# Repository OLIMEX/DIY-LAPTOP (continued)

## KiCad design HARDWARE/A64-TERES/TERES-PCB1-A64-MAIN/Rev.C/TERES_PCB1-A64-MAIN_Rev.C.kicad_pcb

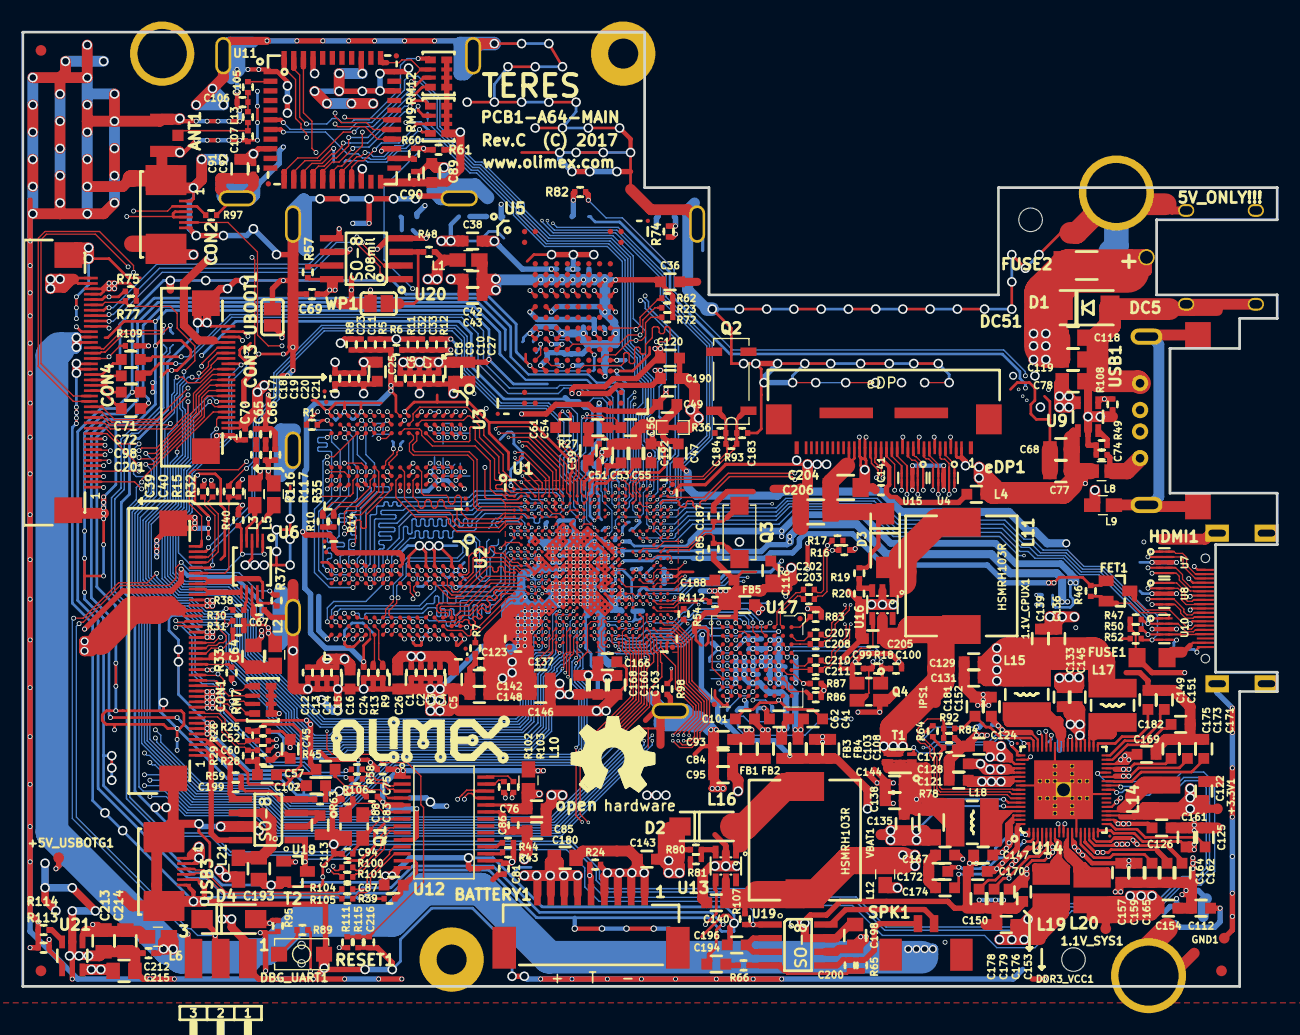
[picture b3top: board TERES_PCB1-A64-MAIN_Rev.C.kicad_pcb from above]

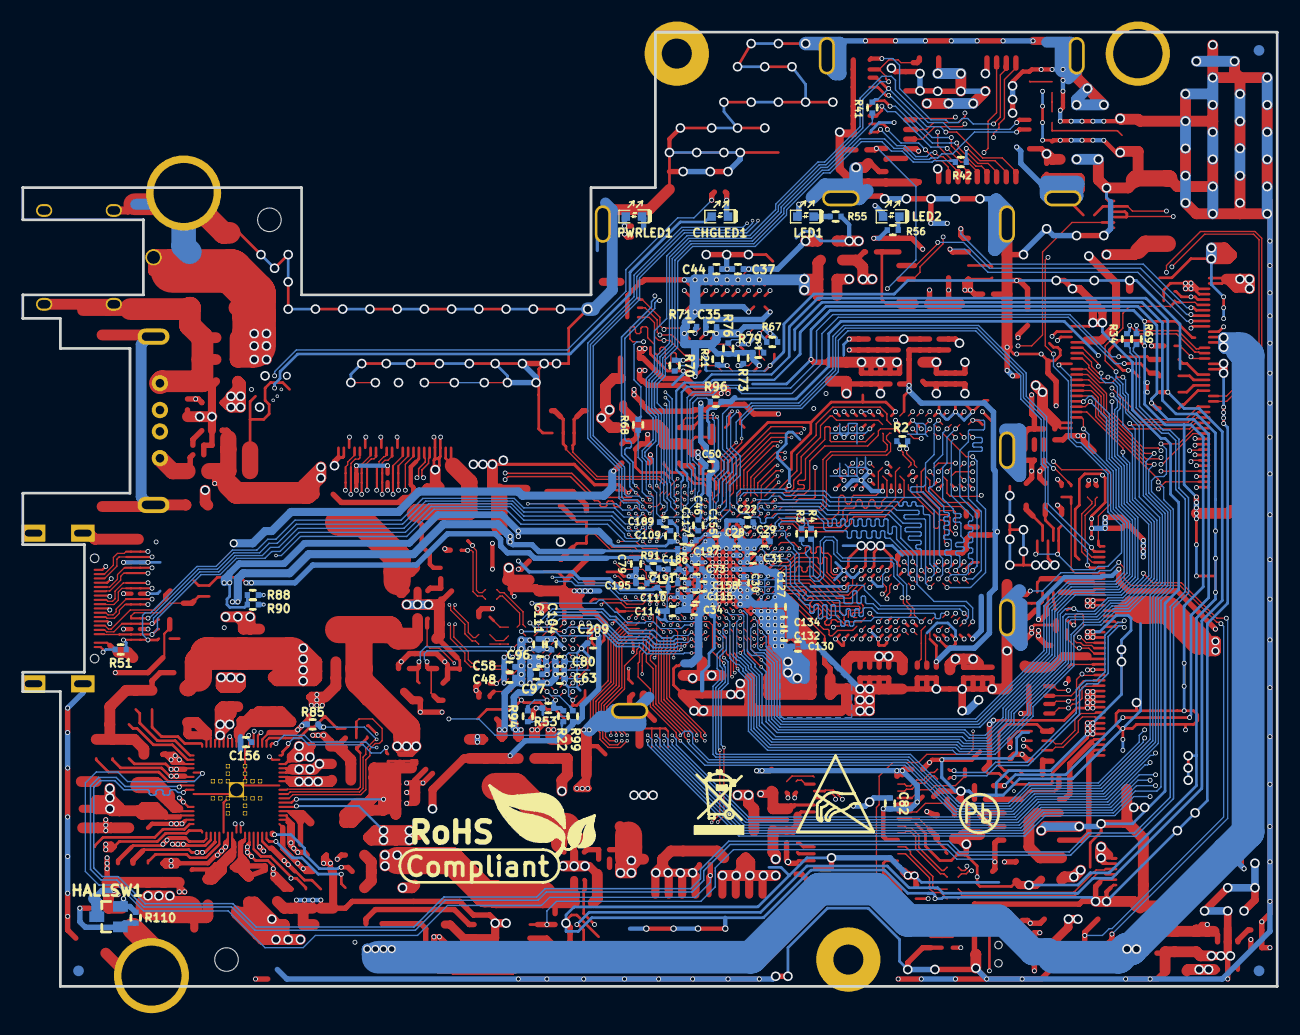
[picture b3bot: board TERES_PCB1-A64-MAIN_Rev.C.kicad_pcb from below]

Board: 6 copper layers, 117.0 x 89.0 mm, 443 parts (75 on the bottom side), 414 nets.

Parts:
1.1V_CPUX1, 1.1V_SYS1: TESTPAD; TESTPAD_40-ROUND
+3.3V1: TESTPAD; TESTPAD_40-ROUND
+5V_USBOTG1: +5V_USBOTG; TESTPAD_40-ROUND
ANT1: PCB_WIFI_ANT; U.FL-R-SMT-1
BATTERY1: BATTCON; BATCONN-TERES
C1, C2, C3, C4, C6, C7, C8, C9, C11, C12, C13, C14, C15, C17, C18, C19, C20, C22, C23, C24, C25, C28, C29, C30, C31, C32, C33, C34, C35, C37, C39, C40, C44, C46, C50, C51, C52, C60, C65, C66, C67, C69, C70, C73, C74, C75, C79, C81, C82, C83, C86, C90, C92, C109, C110, C114, C115, C117, C123, C127, C130, C132, C134, C141, C155, C156, C158, C177, C186, C189, C191, C195, C197, C202, C203, C207, C208, C209, C210, C211, C212, C216: 100nF; C_0402_5MIL_DWS
C5, C10, C16, C21, C26, C42, C47, C49, C53, C54, C57, C59, C89, C91, C116, C121, C122, C124, C125, C126, C128, C129, C131, C133, C136, C138, C139, C140, C143, C144, C145, C146, C147, C148, C149, C150, C151, C152, C153, C154, C157, C159, C161, C162, C164, C165, C166, C167, C168, C169, C170, C171, C172, C173, C175, C176, C178, C179, C188, C192: 10uF/6.3V/0603; C_0603_5MIL_DWS
C27, C36, C38, C43, C45, C55, C71, C72, C98, C102, C112, C113, C120, C135, C137, C142, C160, C163, C181, C182, C190, C194, C196, C201: 1uF/6.3V/0603; C_0603_5MIL_DWS
C41, C62, C93, C101: 4.7uF/6.3V; C_0603_5MIL_DWS
C48, C63, C96, C104: 100nF/6.3V; C_0402_5MIL_DWS
C56, C61: 2.2uF/6.3V/0603; C_0603_5MIL_DWS
C58, C80, C97, C111: 10nF/6.3V; C_0402_5MIL_DWS
C64, C68, C77, C78, C118, C119, C180, C213, C214, C215: 47uF/6.3V/0805; C_0805_5MIL_DWS
C76: 10uF; C_0603_5MIL_DWS
C84, C95, C103, C108, C205: 22uF/6.3V; C_0603_5MIL_DWS
C85: 10uF; R_0603_5MIL_DWS
C87: 1uF; C_0603_5MIL_DWS
C88, C94, C185, C187: 33pF; C_0402_5MIL_DWS
C99, C100: 22pF; C_0402_5MIL_DWS
C105, C183, C184: 10pF; C_0402_5MIL_DWS
C106: 0.8pF; C_0402_5MIL_DWS
C107: 1.5pF; C_0402_5MIL_DWS
C174: NA(10uF/6.3V/0603); C_0603_5MIL_DWS
C193, C198: 47uF; C_0805_5MIL_DWS
C199, C200: 100pF; C_0402_5MIL_DWS
C204, C206: 22uF/25V; C_1206_5MIL_DWS
CHGLED1: LED/RED/0603; LED_0603_KA
CON1, CON4: CONN_01X40; FPV-WZA21-40-LF
CON2: CONN_01X06; FLEXCON-0.5-6
CON3: CONN_01X20; FPV-WZA21-20-LF
D1: SMBJ6.0A; DO214AA
D2, D3, D4: 1N5822/SS34/SMA; SMA-KA
DBG_UART1: NA(HN1x3); HN1x3(SMD)
DC5: PWR-JACK-THERES; DC-055-TERES
DC51: TESTPAD; TESTPAD_40-ROUND
DDR3_VCC1: TESTPAD; TESTPAD_40-ROUND
FB1, FB2, FB3, FB4, FB5: FB0603/600R/200mA; L_0603_5MIL_DWS
FET1: BSS138(SOT23-3); SOT23
FUSE1: FSMD035; FUSE-1206
FUSE2: NA(5025); FUSE-5025
GND1: TESTPAD; TESTPAD_40-ROUND
HALLSW1: TCS40DPR; SOT23
HDMI1: HDMI-SWM-19; HDMI-MINI-TERES
HOLE1, HOLE2, HOLE3, HOLE4, HOLE5, HOLE6, HOLE7, HOLE8, HOLE9: TESTPAD; Oval_Drill
IPS1: TESTPAD; TESTPAD_40-ROUND
L1, L2, L3, L5, L6, L8, L9, L10, L12, L21: FB0805/600R/2A; L_0805_5MIL_DWS
L4: FB0603/600R/200mA; L_0603_5MIL_DWS
L11: HSMRH103R-220M; HSMRH103R
L13: 3.3nH; R_0402_5MIL_DWS
L14, L19, L20: SWPA3015S1R5NT(1.5uH/2.30A/DCR<0.1R/CD32); CD32
L15, L17, L18: SWPA4018S1R5NT(1.5uH/3.35A/DCR<0.1R/CD43); CD42(43)
L16: HSMRH103R-2R5M; HSMRH103R
LED1, LED2: GREEN; LED_0603_KA
MountingHole: Mounting_hole_3.3mm; Mounting_hole_5.6mm_TERES
MountingHole#2: Mounting_hole_3.3mm; Mounting_hole_5.6mm_TERES
MountingHole#3: Mounting_hole_3.3mm
MountingHole#4: Mounting_hole_3.3mm; Mounting_hole_2.8mm
MountingHole#5: Mounting_hole_3.3mm; Mounting_hole_TERES_4.6mm
MountingHole#6, MountingHole#7: Mounting_hole_3.3mm; NPTH_2.2mm
PWRLED1: LED/Green/0603; LED_0603_KA
Q1: 12MHz-20pf; TSX-3.2x2.5mm_GND(3)
Q2: MC-306_32.768KHZ/SMD_8038/6pF; MC306-HS
Q3: 4SB24.000F20E15/5x3.2mm/20ppm/20pF; Q5x3.25
Q4: 27.000MHz/20ppm; TSX-3.2x2.5mm_GND(3)
R1, R5, R8, R11, R12, R74: 2k/1%; R_0402_5MIL_DWS
R2: 100R/1%; R_0402_5MIL_DWS
R3, R4, R33, R34, R41, R42, R54, R58, R68, R69, R100, R101, R102, R103, R104, R105, R106, R116, R117: 22R; R_0402_5MIL_DWS
R6, R62, R70, R71, R72, R73, R76, R79, R96, R97, R98: NA; R_0402_5MIL_DWS
R7, R9, R10: 240R/1%; R_0402_5MIL_DWS
R13, R14: NA(243R/1%); R_0402_5MIL_DWS
R15: 47K; R_0402_5MIL_DWS
R16, R17: (na)100K; R_0402_5MIL_DWS
R18, R32: 1M; R_0402_5MIL_DWS
R19: 22.1K /1%; R_0402_5MIL_DWS
R20: 1.1K/1%; R_0402_5MIL_DWS
R21, R23, R31, R39, R40, R43, R48, R52, R57, R85, R95, R108, R109, R110, R113, R115: 10k; R_0402_5MIL_DWS
R22, R25, R28, R64, R86, R89, R92: 1k; R_0402_5MIL_DWS
R24: NA(10K); R_0402_5MIL_DWS
R26, R29, R55, R56: 1.5k; R_0402_5MIL_DWS
R27: 200k/1%; R_0402_5MIL_DWS
R30, R35, R53: 100k; R_0402_5MIL_DWS
R36: 0R(Board_Mounted); 0R_0603
R37, R38: 220R; R_0402_5MIL_DWS
R44, R46, R67: 47k; R_0402_5MIL_DWS
R45: 680R/1%; R_0603_5MIL_DWS
R47, R50, R82, R87, R88, R90, R94, R99, R112: 2.2k; R_0402_5MIL_DWS
R49: 10k/1%; R_0402_5MIL_DWS
R51, R75, R77, R111: 4.7k; R_0402_5MIL_DWS
R59, R65: 22.1K/1%; R_0402_5MIL_DWS
R60, R91: NA(0R); R_0402_5MIL_DWS
R61: NA(10k); R_0402_5MIL_DWS
R63, R66: 12k/1%; R_0402_5MIL_DWS
R78: 0.01R/1%/1206; R_1206_5MIL_DWS
R80: 8.25k/1%; R_0402_5MIL_DWS
R81: 1.1k/1%; R_0402_5MIL_DWS
R83: 12K_1%; R_0402_5MIL_DWS
R84: na(1k); R_0402_5MIL_DWS
R93: 10M; R_0402_5MIL_DWS
R107: 150K; R_0402_5MIL_DWS
R114: 13k/1%; R_0402_5MIL_DWS
RESET1: IT1185AU2; uTACTIL
RM7, RM9, RM12: RA1206_(4x0603)_4B8_100k; R_MATRIX_4
Ref**: Val**; LOGO_ANTISTATIC_1
Ref**#2: Val**; LOGO_ROHS_1
SPK1: SPK1; CON-SPK-TERES
T1: WPM1481(DFN2X2-6L); DFN2x2-6L
T2: DTC114YKA(SOT-23); SOT23
U1: AllWinner-A64(FBGA396); FBGA396
U2, U3: K4B4G1646Q-HYK0(FBGA-96_256Mx16_DDR3-1600_11-11-1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; FBGA96(HYNIX_SAMSUNG_512MX16_DDR3)
U4, U7, U8, U10, U15: RCLAMP0524P(SLP2510P8); SLP2510P8
U5: MTFC4GACAANA-4M_IT(TBGA100); TBGA100
U6: TS5A23159; VSSOP-10
U9, U21: SY6280AAC(SOT23-5); SOT-23-5
U11: RTL8723BS(ComboModule); RL-SM02BD(RTL8723BS)
U12: GL850G-SO28; SSOP28
U13, U16: MT3608(SOT23-6); SOT23-6
U14: AXP803(QFN68_8x8mm); QFN68
U17: ANX6345; BGA_8x8mm_81p_0.8
U18, U19: TS4871; SO-8
U20: W25Q128FVSSIG; SO-8_208mil
UBOOT1: Open; SJ
USB1: USB_A_THERES; USB-A-TERES
USB3: USB3; FLEXCON-0.5-6
VBAT1: TESTPAD; TESTPAD_40-ROUND
WP1: Open; SJ
eDP1: LCD_CONN; eDP-TERES

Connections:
1.1V_CPUS: C117.2, C120.2, C179.2, U1.H15, U14.5
1.1V_CPUX: 1.1V_CPUX1.1, C123.2, C127.2, C129.2, C130.2, C131.2, C132.2, C134.2, C136.2, C137.2, C139.2, C142.2, C146.2, C148.2, L15.2, L17.2, U1.AA1, U1.AA3, U1.AB2, U1.AC1, U1.AC2, U1.U6, U1.V2, U1.V3, U1.V4, U1.V5, U1.V6, U1.W1, U1.W3, U1.W4, U1.W5, U1.Y2, U1.Y3, U1.Y4
1.1V_SYS: 1.1V_SYS1.1, C154.2, C155.2, C158.2, C160.2, C163.2, C166.2, C168.2, L20.2, U1.J12, U1.J13, U1.K14, U1.L13, U1.L14, U1.M13, U1.M14, U1.N14, U1.P14, U1.R13, U1.R14, U1.T15, U14.9
1.2V_HSIC: C178.2, C197.1, CON3.17, U1.K16, U14.3
3.0V_RTC: C152.1, C189.2, C190.2, R85.2, U1.H16, U14.49
#DEBUGSELECT: R40.2, U1.D20, U6.1, U6.5
+1.5V: C1.1, C2.1, C3.1, C4.1, C5.1, C6.1, C7.1, C8.1, C9.1, C10.1, C11.1, C12.1, C13.1, C14.1, C15.1, C16.1, C17.1, C18.1, C19.1, C20.1, C21.1, C26.1, C27.1, C28.1, C29.1, C30.1, C31.1, C32.2, C150.2, DDR3_VCC1.1, L19.2, R1.2, R5.2, R11.2, U1.G7, U1.G8, U1.G9, U1.J8, U1.K6, U1.K7, U1.L6, U1.L7, U1.L8, U1.N7, U1.N8, U2.A1, U2.A8, U2.B2, U2.C1, U2.C9, U2.D2, U2.D9, U2.E9, U2.F1, U2.G7, U2.H2, U2.H9, U2.K2, U2.K8, U2.N1, U2.N9, U2.R1, U2.R9, U3.A1, U3.A8, U3.B2, U3.C1, U3.C9, U3.D2, U3.D9, U3.E9, U3.F1, U3.G7, U3.H2, U3.H9, U3.K2, U3.K8, U3.N1, U3.N9, U3.R1, U3.R9, U14.8
+1V8: C47.2, C50.2, C170.2, U1.E13, U14.68
+3.0VA: C46.1, C49.1, C175.1, C191.2, R32.2, U1.G14, U1.N16, U14.31
+3.3VD: C79.2, C161.2, FET1.1, R46.1, U1.M16, U14.17
+3V3: +3.3V1.1, C34.2, C69.2, C70.2, C73.2, C91.2, C92.2, C112.2, C114.2, C115.2, C116.2, C122.2, C195.2, CON3.1, CON3.2, CON4.37, CON4.38, HALLSW1.1, L1.1, L2.1, L14.2, R16.1, R30.2, R31.2, R48.2, R57.2, R74.1, R75.1, R77.1, R91.1, R95.2, R109.2, R110.2, RM7.1.1, RM7.2.1, RM7.3.1, RM7.4.1, U1.L16, U1.N19, U1.R16, U1.T14, U1.U15, U1.U18, U11.9, U13.4, U14.20, U20.8, eDP1.1, eDP1.2
+5V: C78.1, C143.2, C215.1, D2.1, R80.1, U9.5, U21.5
/NAND Flash , eMMC, T-Card and Audio/FC_MIC_N: C60.1, CON1.8, R29.1
/NAND Flash , eMMC, T-Card and Audio/FC_MIC_P: C52.1, CON1.9, R26.1
/NAND Flash , eMMC, T-Card and Audio/HBIAS: CON1.40, U1.D13
/NAND Flash , eMMC, T-Card and Audio/HP-DET: R15.2, U1.D11
/NAND Flash , eMMC, T-Card and Audio/HPOUTL: L5.1, R35.2, R117.2, U1.C13
/NAND Flash , eMMC, T-Card and Audio/HPOUTR: L3.1, R116.2, U1.C12
/NAND Flash , eMMC, T-Card and Audio/HS-MIC: CON1.39, U1.B10
/NAND Flash , eMMC, T-Card and Audio/HUSB2-D+: CON1.25, R106.1
/NAND Flash , eMMC, T-Card and Audio/HUSB2-D-: CON1.26, R58.1
/NAND Flash , eMMC, T-Card and Audio/MBIAS: C45.2, R25.2, U1.E14
/NAND Flash , eMMC, T-Card and Audio/MICIN1_N: C60.2, U1.B16
/NAND Flash , eMMC, T-Card and Audio/MICIN1_P: C52.2, U1.B15
/NAND Flash , eMMC, T-Card and Audio/MICIN2+: C39.2, CON1.38
/NAND Flash , eMMC, T-Card and Audio/MICIN2-: C40.2, CON1.37
/NAND Flash , eMMC, T-Card and Audio/MICIN2_N: C40.1, U1.A17
/NAND Flash , eMMC, T-Card and Audio/MICIN2_P: C39.1, U1.B17
/NAND Flash , eMMC, T-Card and Audio/SDC0-CLK: R33.2, U1.AC8
/NAND Flash , eMMC, T-Card and Audio/SDC0-CMD: CON1.20, R31.1, U1.W9
/NAND Flash , eMMC, T-Card and Audio/SDC0-D0: CON1.16, RM7.3.2, U1.W13
/NAND Flash , eMMC, T-Card and Audio/SDC0-D1: CON1.15, RM7.2.2, U1.AB10
/NAND Flash , eMMC, T-Card and Audio/SDC0-D2: CON1.22, RM7.4.2, U1.AB9
/NAND Flash , eMMC, T-Card and Audio/SDC0-D3: CON1.21, R30.1, U1.AB6
/NAND Flash , eMMC, T-Card and Audio/SDC0-DET#: CON1.14, RM7.1.2, U1.AB8
/NAND Flash , eMMC, T-Card and Audio/SDC2-CLK: R68.2, U1.G20
/NAND Flash , eMMC, T-Card and Audio/SDC2-CMD: R21.1, U1.K19, U5.P5
/NAND Flash , eMMC, T-Card and Audio/SDC2-D0: R67.1, U1.M21, U5.K2
/NAND Flash , eMMC, T-Card and Audio/SDC2-D1: R79.1, U1.L19, U5.N2
/NAND Flash , eMMC, T-Card and Audio/SDC2-D2: R76.1, U1.K20, U5.K3
/NAND Flash , eMMC, T-Card and Audio/SDC2-D3: R73.1, U1.H20, U5.N3
/NAND Flash , eMMC, T-Card and Audio/SDC2-D4: R72.1, U1.P18, U5.N8
/NAND Flash , eMMC, T-Card and Audio/SDC2-D5: R71.1, U1.L20, U5.K8
/NAND Flash , eMMC, T-Card and Audio/SDC2-D6: R70.1, U1.J21, U5.N9
/NAND Flash , eMMC, T-Card and Audio/SDC2-D7: R62.1, U1.R21, U5.K9
/NAND Flash , eMMC, T-Card and Audio/SDC2-RST: R23.1, U1.N20, U5.M5
/NAND Flash , eMMC, T-Card and Audio/SPKR_N: C199.1, CON1.3, CON1.4, R59.1, U18.5
/NAND Flash , eMMC, T-Card and Audio/SPKR_P: CON1.1, CON1.2, U18.8
/Power Supply, Extensions and MiPi-DSI/AXP_USB+: R34.1, U14.26
/Power Supply, Extensions and MiPi-DSI/AXP_USB-: R69.1, U14.27
/Power Supply, Extensions and MiPi-DSI/DC5SET: R84.2, R92.1, U14.62
/Power Supply, Extensions and MiPi-DSI/HS_DAT: CON3.19, U1.G19
/Power Supply, Extensions and MiPi-DSI/HS_STR: CON3.18, U1.H19
/Power Supply, Extensions and MiPi-DSI/JTAGSEL0: CON2.2, R97.1, U1.AA11
/Power Supply, Extensions and MiPi-DSI/PB0: CON4.16, U1.V9
/Power Supply, Extensions and MiPi-DSI/PB1: CON4.15, U1.AB7
/Power Supply, Extensions and MiPi-DSI/PB2: CON4.14, U1.W10
/Power Supply, Extensions and MiPi-DSI/PB3: CON4.13, U1.AA7
/Power Supply, Extensions and MiPi-DSI/PB4: CON3.6, U1.W7
/Power Supply, Extensions and MiPi-DSI/PB5: CON3.5, U1.AA6
/Power Supply, Extensions and MiPi-DSI/PB6: CON3.4, U1.W8
/Power Supply, Extensions and MiPi-DSI/PB7: CON3.3, U1.Y6
/Power Supply, Extensions and MiPi-DSI/PE0: CON4.12, U1.AA18
/Power Supply, Extensions and MiPi-DSI/PE1: CON4.11, U1.AB23
/Power Supply, Extensions and MiPi-DSI/PE2: CON4.10, U1.AA22
/Power Supply, Extensions and MiPi-DSI/PE3: CON4.9, U1.AA21
/Power Supply, Extensions and MiPi-DSI/PE4: CON4.8, U1.AA19
/Power Supply, Extensions and MiPi-DSI/PE5: CON4.7, U1.W17
/Power Supply, Extensions and MiPi-DSI/PE6: CON4.6, U1.W20
/Power Supply, Extensions and MiPi-DSI/PE7: CON4.5, U1.Y19
/Power Supply, Extensions and MiPi-DSI/PE8: CON4.4, U1.AC22
/Power Supply, Extensions and MiPi-DSI/PE9: CON4.3, U1.Y17
/Power Supply, Extensions and MiPi-DSI/PE10: CON4.2, U1.AB22
/Power Supply, Extensions and MiPi-DSI/PE11: CON4.1, U1.W21
/Power Supply, Extensions and MiPi-DSI/PE12: CON3.12, U1.AB20
/Power Supply, Extensions and MiPi-DSI/PE13: CON3.11, U1.Y22
/Power Supply, Extensions and MiPi-DSI/PE14: CON3.10, U1.AC20
/Power Supply, Extensions and MiPi-DSI/PE15: CON3.9, U1.Y23
/Power Supply, Extensions and MiPi-DSI/PE16: CON3.8, U1.AB21
/Power Supply, Extensions and MiPi-DSI/PE17: CON3.7, U1.W22
/R_S0SCK_N: R4.2, U1.G3
/R_S0SCK_P: R3.2, U1.G2
/S0SA0: U1.P5, U2.N3, U3.N3
/S0SA1: U1.R4, U2.P7, U3.P7
/S0SA2: U1.N5, U2.P3, U3.P3
/S0SA3: U1.N6, U2.N2, U3.N2
/S0SA4: U1.P6, U2.P8, U3.P8
/S0SA5: U1.G4, U2.P2, U3.P2
/S0SA6: U1.F3, U2.R8, U3.R8
/S0SA7: U1.E4, U2.R2, U3.R2
/S0SA8: U1.D3, U2.T8, U3.T8
/S0SA9: U1.C4, U2.R3, U3.R3
/S0SA10: U1.M4, U2.L7, U3.L7
/S0SA11: U1.U4, U2.R7, U3.R7
/S0SA12: U1.K5, U2.N7, U3.N7
/S0SA13: U1.E8, U2.T3, U3.T3
/S0SA14: U1.K4, U2.T7, U3.T7
/S0SA15: U1.T4, U2.M7, U3.M7
/S0SBA0: U1.D8, U2.M2, U3.M2
/S0SBA1: U1.R3, U2.N8, U3.N8
/S0SBA2: U1.C6, U2.M3, U3.M3
/S0SCAS: U1.C9, U2.K3, U3.K3
/S0SCKE0: U1.J3, U2.K9, U3.K9
/S0SCKE1: U1.H6, U2.J9, U3.J9
/S0SCK_N: R2.1, R4.1, U2.K7, U3.K7
/S0SCK_P: R2.2, R3.1, U2.J7, U3.J7
/S0SCS0: U1.E5, U2.L2, U3.L2
/S0SCS1: U1.H5, U2.L1, U3.L1
/S0SDQ0: U1.L3, U2.F7
/S0SDQ1: U1.G1, U2.G2
/S0SDQ2: U1.H3, U2.F2
/S0SDQ3: U1.K1, U2.H7
/S0SDQ4: U1.H2, U2.E3
/S0SDQ5: U1.H1, U2.H3
/S0SDQ6: U1.L1, U2.H8
/S0SDQ7: U1.L2, U2.F8
/S0SDQ8: U1.T3, U2.A7
/S0SDQ9: U1.T2, U2.C8
/S0SDQ10: U1.T1, U2.B8
/S0SDQ11: U1.R2, U2.D7
/S0SDQ12: U1.N3, U2.A3
/S0SDQ13: U1.N2, U2.C2
/S0SDQ14: U1.N1, U2.C3
/S0SDQ15: U1.M2, U2.A2
/S0SDQ16: U1.E3, U3.F7
/S0SDQ17: U1.F2, U3.H8
/S0SDQ18: U1.E2, U3.H7
/S0SDQ19: U1.E1, U3.F8
/S0SDQ20: U1.B1, U3.E3
/S0SDQ21: U1.B2, U3.H3
/S0SDQ22: U1.A2, U3.G2
/S0SDQ23: U1.B3, U3.F2
/S0SDQ24: U1.C5, U3.B8
/S0SDQ25: U1.B4, U3.D7
/S0SDQ26: U1.A4, U3.C8
/S0SDQ27: U1.A5, U3.A7
/S0SDQ28: U1.A7, U3.C3
/S0SDQ29: U1.A8, U3.C2
/S0SDQ30: U1.B8, U3.A3
/S0SDQ31: U1.B9, U3.A2
/S0SDQM0: U1.J2, U2.E7
/S0SDQM1: U1.P3, U2.D3
/S0SDQM2: U1.C2, U3.E7
/S0SDQM3: U1.B7, U3.D3
/S0SDQS0_N: U1.K2, U2.G3
/S0SDQS0_P: U1.K3, U2.F3
/S0SDQS1_N: U1.P2, U2.B7
/S0SDQS1_P: U1.P1, U2.C7
/S0SDQS2_N: U1.D1, U3.G3
/S0SDQS2_P: U1.D2, U3.F3
/S0SDQS3_N: U1.B5, U3.B7
/S0SDQS3_P: U1.B6, U3.C7
/S0SODT0: U1.D5, U2.K1, U3.K1
/S0SODT1: U1.E7, U2.J1, U3.J1
/S0SRAS: U1.F7, U2.J3, U3.J3
/S0SRST: R1.1, U1.D10, U2.T2, U3.T2
/S0SVREF: C22.2, C32.1, C33.2, R6.2, R11.1, R12.2, U1.G5
/S0SWE: U1.C8, U2.L3, U3.L3
/USB&HDMI,WiFi&BT,Ethernet,LCD/AP-WAKE-BT: U1.B20, U11.6
/USB&HDMI,WiFi&BT,Ethernet,LCD/BT-PCM-CLK: U1.AB18, U11.26
/USB&HDMI,WiFi&BT,Ethernet,LCD/BT-PCM-DIN: U1.AC19, U11.27
/USB&HDMI,WiFi&BT,Ethernet,LCD/BT-PCM-DOUT: U1.U22, U11.25
/USB&HDMI,WiFi&BT,Ethernet,LCD/BT-PCM-SYNC: U1.AB19, U11.28
/USB&HDMI,WiFi&BT,Ethernet,LCD/BT-RST-N: RM12.3.2, U1.A20, U11.34
/USB&HDMI,WiFi&BT,Ethernet,LCD/BT-UART-CTS: U1.AC17, U11.44
/USB&HDMI,WiFi&BT,Ethernet,LCD/BT-UART-RX: RM12.4.2, U1.AB17, U11.43
/USB&HDMI,WiFi&BT,Ethernet,LCD/BT-UART-TX: U1.U23, U11.42
/USB&HDMI,WiFi&BT,Ethernet,LCD/BT-WAKE-AP: U1.D19, U11.7
/USB&HDMI,WiFi&BT,Ethernet,LCD/HCEC: FET1.2, R46.2, U1.F21, U10.1, U10.10
/USB&HDMI,WiFi&BT,Ethernet,LCD/HHPD: R51.1, R52.1, U1.E21, U10.5, U10.6
/USB&HDMI,WiFi&BT,Ethernet,LCD/HSCL: HDMI1.15, R47.2, U1.G21, U10.2, U10.9
/USB&HDMI,WiFi&BT,Ethernet,LCD/HSDA: HDMI1.16, R50.2, U1.E20, U10.4, U10.7
/USB&HDMI,WiFi&BT,Ethernet,LCD/HTX0_N: HDMI1.9, U1.G23, U8.2, U8.9
/USB&HDMI,WiFi&BT,Ethernet,LCD/HTX0_P: HDMI1.8, U1.G22, U8.1, U8.10
/USB&HDMI,WiFi&BT,Ethernet,LCD/HTX1_N: HDMI1.6, U1.F22, U7.5, U7.6
/USB&HDMI,WiFi&BT,Ethernet,LCD/HTX1_P: HDMI1.5, U1.E23, U7.4, U7.7
/USB&HDMI,WiFi&BT,Ethernet,LCD/HTX2_N: HDMI1.3, U1.E22, U7.2, U7.9
/USB&HDMI,WiFi&BT,Ethernet,LCD/HTX2_P: HDMI1.2, U1.D23, U7.1, U7.10
/USB&HDMI,WiFi&BT,Ethernet,LCD/HTXC_N: HDMI1.12, U1.H23, U8.5, U8.6
/USB&HDMI,WiFi&BT,Ethernet,LCD/HTXC_P: HDMI1.11, U1.H22, U8.4, U8.7
/USB&HDMI,WiFi&BT,Ethernet,LCD/HUSB1-D+: R103.1, USB1.3
/USB&HDMI,WiFi&BT,Ethernet,LCD/HUSB1-D-: R102.1, USB1.2
/USB&HDMI,WiFi&BT,Ethernet,LCD/HUSB1-D_N: R102.2, U12.27
/USB&HDMI,WiFi&BT,Ethernet,LCD/HUSB1-D_P: R103.2, U12.28
/USB&HDMI,WiFi&BT,Ethernet,LCD/HUSB4-D+: R105.1, USB3.4
/USB&HDMI,WiFi&BT,Ethernet,LCD/HUSB4-D-: R104.1, USB3.3
/USB&HDMI,WiFi&BT,Ethernet,LCD/HUSB4-D_N: R104.2, U12.11
/USB&HDMI,WiFi&BT,Ethernet,LCD/HUSB4-D_P: R105.2, U12.12
/USB&HDMI,WiFi&BT,Ethernet,LCD/USB0-VBUSDET: C216.2, R111.1, R115.2, U1.AB4
/USB&HDMI,WiFi&BT,Ethernet,LCD/USB1-DRV: R108.2, U1.C19, U9.4
/USB&HDMI,WiFi&BT,Ethernet,LCD/USB1-D_N: U1.C22, U12.25
/USB&HDMI,WiFi&BT,Ethernet,LCD/USB1-D_P: U1.B23, U12.26
/USB&HDMI,WiFi&BT,Ethernet,LCD/WL-PMU-EN: R41.1, RM12.2.2, U11.12
/USB&HDMI,WiFi&BT,Ethernet,LCD/WL-SDIO-CLK: R54.2, U1.V21
/USB&HDMI,WiFi&BT,Ethernet,LCD/WL-SDIO-CMD: RM9.3.2, U1.U20, U11.16
/USB&HDMI,WiFi&BT,Ethernet,LCD/WL-SDIO-D0: RM9.1.2, U1.U19, U11.18
/USB&HDMI,WiFi&BT,Ethernet,LCD/WL-SDIO-D1: RM9.2.2, U1.V22, U11.19
/USB&HDMI,WiFi&BT,Ethernet,LCD/WL-SDIO-D2: RM9.4.2, U1.Y21, U11.14
/USB&HDMI,WiFi&BT,Ethernet,LCD/WL-SDIO-D3: RM12.1.2, U1.W23, U11.15
/USB&HDMI,WiFi&BT,Ethernet,LCD/WL-WAKE-AP: R42.1, U11.13
/VREF0_DDR3: C11.2, C23.1, C24.1, C25.1, R5.1, R6.1, R8.2, U2.H1, U2.M8, U3.H1, U3.M8
/eDP LCD/1.2V: C93.2, C96.2, C97.2, FB1.2, U17.F4, U17.F5, U17.F6
/eDP LCD/2.5V: C62.2, C63.2, C80.2, FB3.2, U17.E7, U17.F7, U17.G4, U17.G5
/eDP LCD/A1.2V: C101.2, C104.2, C111.2, FB2.2, U17.D4, U17.E4
/eDP LCD/A2.5V: C41.2, C48.2, C58.2, FB4.2, U17.C3, U17.C4, U17.C5, U17.C6, U17.C7, U17.D3
/eDP LCD/BKLT_ON: U1.AC10, U15.5, U15.6, U16.4, eDP1.14
/eDP LCD/BKLT_PWM: U1.Y13, eDP1.15
/eDP LCD/EDP_AUX+: C202.1, U17.C1
/eDP LCD/EDP_AUX-: C203.1, U17.B1
/eDP LCD/EDP_AUX_N: C203.2, R16.2, U4.2, U4.9, eDP1.5
/eDP LCD/EDP_AUX_P: C202.2, R17.2, U4.1, U4.10, eDP1.4
/eDP LCD/EDP_HPD_CON: R22.2, U15.4, U15.7, eDP1.13
/eDP LCD/EDP_LANE0+: C207.1, U17.A2
/eDP LCD/EDP_LANE0-: C208.1, U17.A3
/eDP LCD/EDP_LANE0_N: C208.2, U4.4, U4.7, eDP1.7
/eDP LCD/EDP_LANE0_P: C207.2, U4.5, U4.6, eDP1.8
/eDP LCD/EDP_LANE1+: C210.1, U17.A5
/eDP LCD/EDP_LANE1-: C211.1, U17.A6
/eDP LCD/EDP_LANE1_N: C211.2, U15.1, U15.10, eDP1.10
/eDP LCD/EDP_LANE1_P: C210.2, U15.2, U15.9, eDP1.11
/eDP LCD/HUSB3+: R101.2, eDP1.18
/eDP LCD/HUSB3-: R100.2, eDP1.17
/eDP LCD/LCDB2: U1.AA20, U17.H8
/eDP LCD/LCDB3: U1.AA17, U17.H7
/eDP LCD/LCDB4: U1.W19, U17.H6
/eDP LCD/LCDB5: U1.AA14, U17.J8
/eDP LCD/LCDB6: U1.V18, U17.J7
/eDP LCD/LCDB7: U1.AA15, U17.J6
/eDP LCD/LCDCL: U1.AB13, U17.J4
/eDP LCD/LCDDE: U1.AB12, U17.H9
/eDP LCD/LCDG2: U1.Y11, U17.H4
/eDP LCD/LCDG3: U1.AA16, U17.J2
/eDP LCD/LCDG4: U1.V17, U17.J1
/eDP LCD/LCDG5: U1.AA13, U17.H2
/eDP LCD/LCDG6: U1.W16, U17.H3
/eDP LCD/LCDG7: U1.Y16, U17.H1
/eDP LCD/LCDHS: U1.AB11, U17.G9
/eDP LCD/LCDR2: U1.AC16, U17.F2
/eDP LCD/LCDR3: U1.AB16, U17.E2
/eDP LCD/LCDR4: U1.AB15, U17.F1
/eDP LCD/LCDR5: U1.AB14, U17.D2
/eDP LCD/LCDR6: U1.AC14, U17.D1
/eDP LCD/LCDR7: U1.AC13, U17.C2
/eDP LCD/LCDVS: U1.AC11, U17.F8
/eDP LCD/VDC18V: C204.1, C206.1, D3.1, R19.1, eDP1.21, eDP1.22
/eDP LCD/eDP_AGND: C41.1, C48.1, C58.1, C101.1, C104.1, C111.1, FB5.1, U17.A4, U17.A7, U17.B9, U17.E3, U17.F3, U17.G3
/eDP LCD/eDP_RESET: R87.1, U1.Y14, U17.B6
AP-CK32KO: R60.2, R61.1, U1.B18
AP-NMI#: R85.1, U1.G18, U14.61
AP-RESET#: C156.2, R89.2, U1.E17, U14.46
FC_HPDET: CON1.35, R15.1, R32.1
FC_HPOUTFB: CON1.36, U1.C10
FC_HPOUTL: L5.2, U6.2
FC_HPOUTR: L3.2, U6.4
GND: ANT1.2, BATTERY1.0, BATTERY1.1, BATTERY1.2, BATTERY1.3, BATTERY1.4, C1.2, C2.2, C3.2, C4.2, C5.2, C6.2, C7.2, C8.2, C9.2, C10.2, C12.2, C13.2, C14.2, C15.2, C16.2, C17.2, C18.2, C19.2, C20.2, C21.2, C22.1, C23.2, C24.2, C25.2, C26.2, C27.2, C28.2, C29.2, C30.2, C31.2, C33.1, C34.1, C35.1, C36.1, C37.1, C38.1, C42.2, C43.2, C44.2, C62.1, C63.1, C64.2, C67.2, C68.1, C69.1, C70.1, C73.1, C74.2, C75.2, C76.2, C77.1, C78.2, C79.1, C80.1, C81.2, C82.2, C83.2, C84.2, C85.1, C86.2, C87.2, C88.2, C89.1, C90.1, C91.1, C92.1, C93.1, C94.2, C95.2, C96.1, C97.1, C99.2, C100.1, C103.2, C106.1, C107.1, C108.2, C109.2, C110.1, C112.1, C113.2, C114.1, C115.1, C116.1, C117.1, C118.1, C119.1, C120.1, C121.2, C122.1, C123.1, C124.2, C125.1, C126.1, C127.1, C128.2, C129.1, C130.1, C131.1, C132.1, C133.1, C134.1, C136.1, C137.1, C138.2, C139.1, C140.1, C141.2, C142.1, C143.1, C144.2, C145.1, C146.1, C147.2, C148.1, C149.2, C150.1, C151.2, C152.2, C153.1, C154.1, C155.1, C156.1, C157.1, C158.1, C159.1, C160.1, C161.1, C162.1, C163.1, C164.1, C165.1, C166.1, C167.1, C168.1, C169.2, C170.1, C171.2, C172.1, C173.2, C174.1, C175.2, C176.1, C177.1, C178.1, C179.1, C180.1, C181.1, C182.1, C183.2, C184.2, C185.2, C186.1, C187.2, C188.1, C189.1, C190.1, C191.1, C192.1, C193.2, C195.1, C196.2, C197.2, C198.2, C204.2, C205.2, C206.2, C209.2, C212.2, C213.1, C214.1, C215.2, C216.1, CON1.0, CON1.5, CON1.6, CON1.7, CON1.10, CON1.11, CON1.12, CON1.13, CON1.17, CON1.23, CON1.24, CON1.29, CON1.30, CON2.0, CON2.1, CON2.6, CON3.0, CON3.20, CON4.0, CON4.23, CON4.24, D1.A, DBG_UART1.1, DC5.2, FB5.2, GND1.1, HALLSW1.3, HDMI1.0, HDMI1.1, HDMI1.4, HDMI1.7, HDMI1.10, HDMI1.13, HOLE1.1, HOLE2.1, HOLE3.1, HOLE4.1, HOLE5.1, HOLE6.1, HOLE7.1, HOLE8.1, HOLE9.1, L9.1, PWRLED1.1, Q1.3, Q4.3, R7.1, R8.1, R9.2, R10.2, R12.1, R13.2, R14.2, R17.1, R20.2, R24.2, R36.1, R40.1, R45.1, R49.1, R52.2, R53.2, R55.2, R56.2, R81.2, R83.2, R84.1, R86.2, R87.2, R96.2, R97.2, R98.2, R108.1, R112.2, R113.1, R114.1, R115.1, RESET1.2, SPK1.0, T2.2, U1.A1, U1.A23, U1.AC23, U1.C3, U1.C7, U1.D7, U1.G6, U1.G11, U1.H4, U1.H13, U1.J9, U1.J10, U1.J11, U1.J14, U1.J15, U1.K8, U1.K9, U1.K10, U1.K11, U1.K12, U1.K13, U1.L4, U1.L5, U1.L9, U1.L10, U1.L11, U1.L12, U1.L15, U1.M3, U1.M8, U1.M9, U1.M10, U1.M11, U1.M12, U1.M15, U1.N4, U1.N9, U1.N10, U1.N11, U1.N12, U1.N13, U1.N15, U1.P7, U1.P8, U1.P9, U1.P10, U1.P11, U1.P12, U1.P13, U1.R5, U1.R6, U1.R7, U1.R8, U1.R9, U1.R10, U1.R11, U1.R12, U1.R15, U1.T8, U1.T9, U1.T10, U1.T11, U1.T12, U1.T13, U1.U2, U1.U5, U1.U7, U1.U8, U1.U9, U1.U11, U1.U12, U1.V8, U1.V14, U2.A9, U2.B1, U2.B3, U2.B9, U2.D1, U2.D8, U2.E1, U2.E2, U2.E8, U2.F9, U2.G1, U2.G8, U2.G9, U2.J2, U2.J8, U2.M1, U2.M9, U2.P1, U2.P9, U2.T1, U2.T9, U3.A9, U3.B1, U3.B3, U3.B9, U3.D1, U3.D8, U3.E1, U3.E2, U3.E8, U3.F9, U3.G1, U3.G8, U3.G9, U3.J2, U3.J8, U3.M1, U3.M9, U3.P1, U3.P9, U3.T1, U3.T9, U4.3, U4.8, U5.G2, U5.G3, U5.G4, U5.G5, U5.G6, U5.G7, U5.G8, U5.G9, U5.H2, U5.H9, U5.L3, U5.L8, U5.M4, U5.M7, U5.P2, U5.P9, U6.3, U7.3, U7.8, U8.3, U8.8, U9.2, U10.3, U10.8, U11.1, U11.20, U11.31, U11.33, U11.36, U11.41, U12.14, U12.15, U13.2, U14.12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
GNDA: C45.1, C46.2, C47.1, C49.2, C50.1, C51.2, C53.2, C54.1, C55.2, C56.1, C59.2, C65.1, C66.1, R27.2, R28.2, R35.1, R36.2, U1.A11
HUSB2-D_N: R58.2, U12.2
HUSB2-D_P: R106.2, U12.3
HUSB3-D_N: R100.1, U12.8
HUSB3-D_P: R101.1, U12.9
IC-CLK: CON4.32, U1.P20, U20.6
IC-CS: U1.P19, U20.1
IC-MISO: CON4.33, U1.K18, U20.2
IC-MOSI: CON4.34, U1.T21, U20.5
IPS: C67.1, C126.2, C128.1, C133.2, C140.2, C145.2, C147.1, C153.2, C157.2, C159.2, C167.2, C169.1, C176.2, C205.1, CHGLED1.2, CON4.39, CON4.40, IPS1.1, L11.1, L12.2, L16.1, L21.2, R107.2, T1.4, T1.8, U6.8, U13.5, U14.4, U14.6, U14.11, U14.15, U14.19, U14.22, U14.32, U14.38, U14.39, U14.40, U14.55, U14.56, U14.66, U14.67, U16.5
KEYADC: CON2.5, U1.A16
LED_CAPS: LED1.2, U1.T20
LED_NUML: LED2.2, U1.T19
LIDSW: HALLSW1.2, R110.1, U1.B21
LINEINL: C72.2, U1.B14
LINEINR: C71.2, U1.A14
LINEOUTL: C98.2, C194.2, U1.D16
LINEOUTR: C102.2, C201.2, U1.C16
unnamed: ANT1.1, C107.2, L13.2
unnamed: C35.2, C36.2, C42.1, C43.1, C44.1, L1.2, R21.2, R23.2, R62.2, R67.2, R70.2, R71.2, R72.2, R73.2, R76.2, R79.2, U5.F2, U5.F3, U5.F4, U5.F5, U5.F6, U5.F7, U5.F8, U5.F9, U5.H3, U5.H8, U5.L2, U5.L4, U5.L7, U5.L9, U5.P3, U5.P8
unnamed: C37.2, C38.2, U5.E4
unnamed: C51.1, C53.1, U1.C11
unnamed: C54.2, C56.2, U1.F12, U1.G13
unnamed: C55.1, U1.B12
unnamed: C57.1, R28.1, R29.2
unnamed: C57.2, R25.1, R26.2
unnamed: C59.1, R27.1, U1.B11
unnamed: C61.1, U1.E11
unnamed: C61.2, U1.E10
unnamed: C64.1, CON1.19, L2.2
unnamed: C65.2, R116.1
unnamed: C66.2, R117.1
unnamed: C71.1, CON4.22
unnamed: C72.1, CON4.21
unnamed: C74.1, L8.2, USB1.1
unnamed: C75.1, C82.1, C83.1, L10.2, U12.1, U12.5, U12.10
unnamed: C76.1, C81.1, L10.1, R43.1, R44.1, U12.16, U12.24
unnamed: C87.1, R39.2, U12.13
unnamed: C88.1, Q1.1, U12.6
unnamed: C94.1, Q1.2, U12.7
unnamed: C98.1, CON4.20
unnamed: C99.1, Q4.2, R18.2, U17.B4
unnamed: C100.2, Q4.1, R18.1, U17.B3
unnamed: C102.1, R63.2
unnamed: C105.1, U11.2
unnamed: C105.2, C106.2, L13.1
unnamed: C113.1, U18.2, U18.3
unnamed: C118.2, C119.2, C121.1, D1.C, DC5.1, DC51.1, FUSE2.1, FUSE2.2, U14.57, U14.58
unnamed: C125.2, U14.18
unnamed: C135.1, C138.1, C144.1, L18.1, R78.1, T1.1, T1.2, T1.5, T1.6, T1.7, U14.63
unnamed: C141.1, L4.1, eDP1.16
unnamed: C149.1, U14.35
unnamed: C151.1, U14.34
unnamed: C165.2, U14.13
unnamed: C172.2, U14.1
unnamed: C174.2, U14.2
unnamed: C181.2, R92.2, U14.50
unnamed: C182.2, U14.33
unnamed: C183.1, Q2.2, R93.1, U1.B19
unnamed: C184.1, Q2.1, R93.2, U1.C18
unnamed: C185.1, Q3.1, U1.K23
unnamed: C186.2, R91.2, U1.N18
unnamed: C187.1, Q3.2, U1.K22
unnamed: C188.2, U1.P16
unnamed: C192.2, U1.G16
unnamed: C193.1, L21.1, U18.6
unnamed: C194.1, R66.2
unnamed: C196.1, U19.2, U19.3
unnamed: C198.1, L12.1, U19.6
unnamed: C199.2, R59.2, R63.1, U18.4
unnamed: C200.1, R65.1, SPK1.1, U19.5
unnamed: C200.2, R65.2, R66.1, U19.4
unnamed: C201.1, CON4.19
unnamed: C213.2, C214.2, L6.1, R111.2, U21.1
unnamed: CHGLED1.1, R82.2
unnamed: CON1.18, R33.1
unnamed: CON1.31, CON1.32, U6.6
unnamed: CON1.33, CON1.34, U6.10
unnamed: CON2.3, CON2.4, R64.1
unnamed: D2.2, L16.2, U13.1
unnamed: D3.2, L11.2, U16.1
unnamed: D4.2, R95.1, U1.Y7
unnamed: FET1.3, HDMI1.14
unnamed: FUSE1.2, HDMI1.18
unnamed: HDMI1.19, R51.2
unnamed: L9.2, USB1.0
unnamed: L14.1, U14.21
unnamed: L15.1, U14.43, U14.44
unnamed: L17.1, U14.36, U14.37
unnamed: L18.2, U14.65
unnamed: L19.1, U14.7
unnamed: L20.1, U14.10
unnamed: LED1.1, R55.1
unnamed: LED2.1, R56.1
unnamed: PWRLED1.2, R74.2
unnamed: R7.2, U1.U1
unnamed: R9.1, U2.L8
unnamed: R10.1, U3.L8
unnamed: R13.1, U2.L9
unnamed: R14.1, U3.L9
unnamed: R19.2, R20.1, U16.3
unnamed: R22.1, R53.1, U17.F9
unnamed: R37.1, U6.9
unnamed: R38.1, U6.7
unnamed: R41.2, U1.A19
unnamed: R42.2, U1.E19
unnamed: R43.2, U12.17
unnamed: R44.2, U12.18
unnamed: R45.2, U12.4
unnamed: R48.1, U20.3, WP1.1
unnamed: R49.2, U9.3
unnamed: R54.1, U11.17
unnamed: R57.1, U20.7
unnamed: R60.1, U11.24
unnamed: R68.1, U5.P6
unnamed: R80.2, R81.1, U13.3
unnamed: R82.1, U14.53
unnamed: R83.1, U17.A1
unnamed: R86.1, U17.B7
unnamed: R89.1, RESET1.1
unnamed: R96.1, U1.H14
unnamed: R98.1, U1.AA12
unnamed: R107.1, T2.3, U18.1, U19.1
unnamed: R112.1, U1.U21
unnamed: R114.2, U21.3
unnamed: SPK1.2, U19.8
unnamed: T1.3, U14.52
unnamed: U1.F17, UBOOT1.2
PA-ENABLE: T2.1, U1.D22
PH4: CON3.16, U1.AB5
PH5: CON3.15, U1.AC7
PH7: CON4.31, U1.AC5
PH8: CON4.30, U1.Y10
PH10: CON3.14, U1.Y8
PH11: CON3.13, U1.AA5
PL10: CON4.18, U1.D21
PL11: CON4.17, U1.C20
PMU-SCK: R88.1, U1.D17, U14.47
PMU-SDA: R90.1, U1.C17, U14.48
PWR-BUT: C177.2, R64.2, U14.60
TWI0-SCK: R99.2, U1.W11, U17.E8
TWI0-SDA: R94.2, U1.AA10, U17.E9
TWI1-SCK: CON4.36, R75.2, U1.AC4
TWI1-SDA: CON4.35, R77.2, U1.AA9
T_BAT: BATTERY1.5, R24.1, U14.30
UART0RX: D4.1, DBG_UART1.2, R37.2
UART0TX: DBG_UART1.3, R38.2, U1.V10
USB0-DRV: R113.2, U14.51, U21.4
USB0-D_N: CON4.27, R69.2, U1.B22
USB0-D_P: CON4.26, R34.2, U1.A22
USB0-ID: CON4.25, R109.1, U1.AA8
USB5V: C68.2, C77.2, C85.2, C86.1, CON1.27, CON1.28, FUSE1.1, L4.2, L8.1, R39.1, R47.1, R50.1, U9.1, U12.23, USB3.1, USB3.2
USB5VOTG: +5V_USBOTG1.1, C124.1, C212.1, CON4.28, CON4.29, L6.2, U14.54
VBAT: BATTERY1.6, BATTERY1.7, BATTERY1.8, BATTERY1.9, C135.2, C180.2, R78.2, U14.64, VBAT1.1
VCC-PE: C171.1, U14.28
VCC-PL: C89.2, C90.2, C109.1, C110.2, C173.1, R61.2, R88.2, R90.2, RM9.1.1, RM9.2.1, RM9.3.1, RM9.4.1, RM12.1.1, RM12.2.1, RM12.3.1, RM12.4.1, U1.J16, U1.T17, U11.22, U14.29
VDDFB-CPUX: U1.T6, U14.41, U14.42
eDP_1.2V: C84.1, C95.1, C164.2, FB1.1, FB2.1, U14.14
eDP_2.5V: C103.1, C108.1, C162.2, C209.1, FB3.1, FB4.1, R94.1, R99.1, U1.U16, U14.16

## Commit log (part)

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2017-01-26 Hardware files
2017-01-29 * Added ARM Trusted firmware * Linux Kernel sources * U-Boot Sources
2017-01-29 Revert "* Added ARM Trusted firmware"
    This reverts commit 7bf9b8c44a5f25e1aac19fd17593456e6771502c.
2017-01-29 * Added ARM Trusted Firmwre
2017-01-29 * Added U-Boot sources
2017-01-29 * Added Linux Kernel
2017-01-30 * Added Device Tree for Teres
2017-10-13 Import repos from https://github.com/A64-TERES
2017-10-13 mess
2017-10-13 u-boot
2017-10-13 linux
2017-10-13 stuff
2017-11-03 TERES manual upload
2017-11-06 sunxi-pack-tools,readme and make_rootfs updated.
2017-11-06 added additional packages needed by platform-scripts/install_emmc.sh
2017-11-06 Fixed wrong regex, now script report correct device partitions
2017-11-06 install-arduino-ide.sh added, this script will install Arduino IDE
2017-11-06 readme modified
2017-11-07 Fixed previous commit
2017-11-10 fixed keyboard sleep key
2017-11-10 Changing file permission
2017-11-10 defined KEY_SUSPEND
2017-11-17 manual revision 1.2
2017-11-22 teres1-ledctrl: add more looops
2017-11-27 teres1-audioselect: check for read > 0, loop and cosmetic
2017-12-18 Added schematics files in PDF
2017-12-18 Updated to release version
2017-12-18 added schematics in pdf
2017-12-18 Updated to release
2017-12-18 readme updated
2017-12-21 c204, c206 values fixed
2018-01-15 some values corrected
2018-02-10 teres1-audioselect: cosmetic fixes
2018-02-12 toolchain deps added
2018-02-12 more deps added
2018-03-14 check if su
2018-05-09 Auto-detect root partition
2018-05-18 Code cleanup: formatting, added conditional error
2018-05-18 /README.md derived from https://www.olimex.com/Products/DIY-Laptop/
2018-05-18 Moved DOCS/ to doc/ standard
2018-05-18 Added TERES-A64-{BLACK,WHITE} images for docs
2018-05-18 Added link to DIY kit purchase page
2018-05-18 Added images to /README.md; minor text revision
2018-05-18 Moved TERES-I odt+pdf to doc/manuals/
2018-05-18 Create index.rst
    This file allows public documentation to be compiled and hosted at sites such as <proj>.readthedocs.io
2018-05-18 Partial commit of web-based TERES-I manual
2018-05-19 Added links from guide (index.rst) to /README.md
2018-05-19 Fixed image links
2018-05-19 Mis-labeled image title
2018-05-19 Fixed image path
2018-05-19 Changed to HTML for image size control
2018-05-19 Added facebook+twitter svg light icons
2018-05-19 Relinked facebook+twitter to light svg icons
2018-05-19 Relinked to github+wordpress svg icons
2018-05-19 Made icons into links; still have size issues
2018-05-19 Added 50x50px icons
2018-05-19 50x50 pixel icons to addres sizing issue
2018-05-19 Initial table of contents for DIY kit
2018-05-19 Added kit inventory images
2018-05-19 Premature commit because my computer keeps crashing and losing my data
2018-05-19 Iterative commit of docs as to be cautious
2018-05-19 Another iterative commit
2018-05-19 Last iterative commit for assembly walkthrough
2018-05-19 Need a ! in front of images for them to appear
2018-05-19 Merging documentation (rev1.4) branch into master (#24)
    * /README.md derived from https://www.olimex.com/Products/DIY-Laptop/
    * Moved DOCS/ to doc/ standard
    * Added TERES-A64-{BLACK,WHITE} images for docs
    * Added link to DIY kit purchase page
    * Add OLIMEX logo
    * Added images to /README.md; minor text revision
2018-05-30 Elaboration and introduced sub-sections
2018-05-30 Elaborated on education section
2018-05-30 Moved education information to child page
2018-05-30 Organization and added links
2018-05-30 Elaboration
2018-05-30 Placed hardware detail within the HARDWARE dir
2018-05-31 Reduced image whitespace for inline docs
2018-05-31 Moved old/PCB_NAME -> PCB_NAME/Rev.X<.old>
2018-05-31 Moved old/KiCAD* -> KiCad/*.old
2018-05-31 Redirect sw_building.md to existing readme
2018-05-31 Using README standard naming convention
2018-05-31 Adding *.md filetype for TERES-specific READMEs
2018-05-31 Expand main product overview; add initial FAQ
2018-05-31 Add external link to manual img build
2018-05-31 Added detail of mainline effort
2018-05-31 Create evaluation-board-notice.md
    This document is referenced from https://www.olimex.com/Products/Disclamer/evaluation-board-notice/
2018-05-31 Add evaluation notice
2018-05-31 Move assembly instruction to hardware section
    Link "doc/web/hw_in-the-box.md" to be moved to assembly page.
2018-05-31 Cropped images with: mogrify -trim +repage *
2018-05-31 Add assembled laptop image
    Was missing at some point during the migration
2018-05-31 Link directly to #olimex channel
2018-05-31 Create CONTRIBUTING.md
    Supplemental dev_*.md files need to be created, but I will need some help to complete them.
2018-05-31 Commit msg now has bash formatting
2018-05-31 Add evaluation & contribute links
2018-06-11 relative links fixed
2018-06-13 Link reference to 3rd-party 3D-printed case design
    Maybe this case design can be formally adopted?
2018-06-13 Add TERES-015-LCD11.6 datasheet
2018-06-13 Less ambiguous link text
2018-06-13 Replacing erroneous 103.jpg with DSC_1672-Recovered.png
2018-06-20 Elaborated in docs; added glossary
2018-06-20 Add links
2018-06-23 Minor doc formatting; fixed path
2018-06-24 Add links; minor changes
2018-06-24 Add links; formatting; moving license to own file
2018-06-24 Create LICENSE: Dean Camera's LUFA USB stack
2018-06-24 Fix formatting
2018-06-24 Update issue templates
2018-06-25 Add reference to TERES-019-Camera
2018-08-01 Update sw_updating-os.md
    no upgrade
2018-08-04 Add table of contents; minor tweaks
2018-09-24 install_emmc.sh: fix typo
2018-10-09 Use -j`nproc` instead of -j4
    Using -j`nproc`` rather than -j4 allows scaling based on the number of processors available. nproc is provided in the coreutils package.
2018-10-15 Expand high-level documentation
2018-10-15 Remove identical backups since it's all code versioned
2018-10-15 Add A64 datasheet
2018-10-15 Add detail to feature table
2018-10-15 Minor spec clarification
2018-10-17 Fix a few typos and improve readability
2018-11-12 Update link: ForkSand migrated repos to own domain
2018-11-12 Add link
2018-11-30 enabling dual display mode
2018-11-30 enabling dual display
2018-12-05 Enabling dual display mode (#29)
    * enabling dual display mode
    * Add files via upload
    * enabling dual display
    * Update README.md
    * Delete a64-olinuxino-hdmi.dtb
    * Delete a64-olinuxino-lcd.dtb
2018-12-05 Enable the generic fs load and ls commands
2018-12-05 SPL by default boots eMMC, not SD by ayufan-pine64/u-boot-pine64
2018-12-05 Added scripts to help flashing boot0/uboot only Author : Simon Eisenmann longsleep
    U-Boot config modified to speed up boot process
2018-12-05 Revert "SPL by default boots eMMC, not SD by ayufan-pine64/u-boot-pine64"
    This reverts commit 17c26cc8d330acb3500b1dd974063d740e9f0cd1.
2018-12-05 fixed typo
2018-12-05 MMC Driver ported from BSP3.0
2018-12-05 boot.cmd file added Adopted for Teres/A64-OLinuXino
2018-12-05 Converted boot.cmd to u-boot format
2018-12-05 DTS renamed to new format, for mainline naming compability Build scripts modified to accept new format
2018-12-05 Dual display mode enabled by default Driver modified to support custom HDMI resolutions
2018-12-05 Enable hdmi by default
2018-12-05 Improved install desktop script
2018-12-06 Fixed wrong paths in script
2018-12-06 Clarify/organize touchpad install process
2018-12-07 Fixed typos. Since boot partition detect is done by u-boot, there is no change in kernel part table, so mmcblk0 will be boot device in any case
2018-12-10 mkfs.ext4 build incommpatible with 3.10 kernels ext4, when build on Ubuntu > 16.04
2018-12-17 Added Docker file to init build enviorement and Docker.md with instructions
2018-12-28 Increase specification detail
2018-12-31 Host official torrent locally; link to original & 3P
2018-12-31 Redirect OS download link to local assets to simplify procedure
2018-12-31 Create latest torrent symlinks; update README
2019-01-09 Specify power input connector
2019-01-17 New packages added: audioselect debug_switch
2019-01-17 *Headphone debug disabled by default *Fixed logic error in env_set_debug
2019-01-18 Modified readme
2019-01-18 additional tools needed on host machine
2019-01-18 Fixed directorry change issue
2019-01-18 Add cpio to packages
2019-01-21 Fixed debug port init
2019-01-22 Fixed path
2019-03-04 .gitignore: Ignore binary and temporary files
    Ignore all temporary files created during building Linux kernel
    and image.
2019-03-04 make_rootfs.sh: Make bionic image
    Add an option to generate bionic image for A64-TERES. Fix
    execution locale-gen.
    Suggested-by: Lazar Hristov <lhristov@gmail.com>
2019-03-04 make_simpleimage.sh: Fix on mkfs.ext4 options
    Disable options metadata_csum & 64bit after mkfs.ext4
    using tune2fs. Fixes the following error on boot:
    [ 37.259701] EXT4-fs (mmcblk0p2): couldn't mount as ext3 due to feature incompatibilities
    [ 37.269247] EXT4-fs (mmcblk0p2): couldn't mount as ext2 due to feature incompatibilities
    [ 37.288201] JBD2: Unrecognised features on journal
    [ 37.293429] EXT4-fs (mmcblk0p2): error loading journal
2019-03-04 .gitignore: Ignore temp files during builds
    Avoid warnings like the examples below when showing git status:
    warning: could not open directory 'SOFTWARE/A64-TERES/scripts/teres-build-mqHlyiY5yF/': Permission denied
    warning: could not open directory 'SOFTWARE/A64-TERES/scripts/teres-build-7DBpdkWsab/': Permission denied
    warning: could not open directory 'SOFTWARE/A64-TERES/scripts/teres-build-hxppVthocN/': Permission denied
    warning: could not open directory 'SOFTWARE/A64-TERES/scripts/teres-build-Ii73ok6WQw/': Permission denied
    warning: could not open directory 'SOFTWARE/A64-TERES/scripts/teres-build-59exex9IfW/': Permission denied
2019-03-04 make_rootfs.sh: Ensure paths exists before cat
    Ensure that all paths exists before executing cat. Otherwise
    the rootfs was not properly generated and the image was not
    booting.
    Suggested-by: Lazar Hristov <lhristov@gmail.com>
2019-03-05 make_rootfs.sh: Fix symlink to /etc/resolv.conf
    Resolve failure in name resolution for Ubuntu images.
    Create a symbolic link of /etc/resolv.conf that points to:
    /run/systemd/resolve/stub-resolv.conf /etc/resolv.conf
2019-03-06 make_rootfs.sh: Support building ubuntu with KDE
    Support option kde for building Ubuntu 18.04.2 image for
    A64-Teres with kde-plasma-desktop. This image uses the same
    repositories as bionic.
2019-03-06 make_rootfs.sh: Image for a real geek
    Ubuntu 18.04.2 with dwm, surf web browser, stterm and vim.
    A truly geek look and feel. Inspired by a conversation with
    Vladimir Ivanov and Lazar Hristov during the last weekend.
    Suggested-by: Vladimir Ivanov <vladitx@nucleusys.com>, Lazar Hristov <lhristov@gmail.com>
2019-03-07 make_rootfs.sh: Use ppa:ayufan/pine64-ppa
    Replace ppa:longsleep/ubuntu-pine64-flavour-makers with
    ppa:ayufan/pine64-ppa because it provides better support
    of the same deb packages for both Ubuntu 16.04 xenial and
    Ubuntu 18.04 bionic.
2020-06-09 add BOMs in PDF format PCB1-PCB5
2020-07-08 Added more supports for flashing the atmega32u4 keyboard control chip, for hardware newbies like me
2021-09-25 600 DPI scan of keyboard traces.
    This is a scan of the plastic film under the keyboard keys, made with a Canon MX922 printer.
2022-09-14 PCB1_A64_MAIN_REV_C: Translated in English
    The manufacturer that I sent this to was confused by the bulgarian so I translated this in english.
2022-09-15 guix-shell: Initial commit
    This contributions adds definition for GNU Guix to provide a
    reproducible environment that opens KiCAD 6.0.7.
2022-09-16 Remove the old .pro format
2022-09-16 Missed one `.pro` file
2022-09-16 PCB4_PWR_BTN_A: Update KiCAD and docs
    * Updated on KiCAD 6.0.3
    * Added Stack-up table and graphics
    * Added General Notes to the gerber
    * Replaced BOM with generated one
    * Added README using export from gerber
2022-09-20 Troubleshooting link: missing file -> Olimex forum
2023-04-01 README: Add Similar projects with PPC Tyche
    bcs peer-based promotion is important and helps with an adoption
2023-04-02 README: More verbose specifications
2023-04-02 Add datasheet for emmc
2023-04-02 Add datasheet for ram
2023-04-03 Upload
    RAM datasheet
2024-01-19 Add Datasheet for SPI Flash
2024-03-14 README: Add link on OFTC #teres
    Add an IRC room used by teres users to talk and work on the device
2024-06-07 Added link to extensive linux-sunxi page
